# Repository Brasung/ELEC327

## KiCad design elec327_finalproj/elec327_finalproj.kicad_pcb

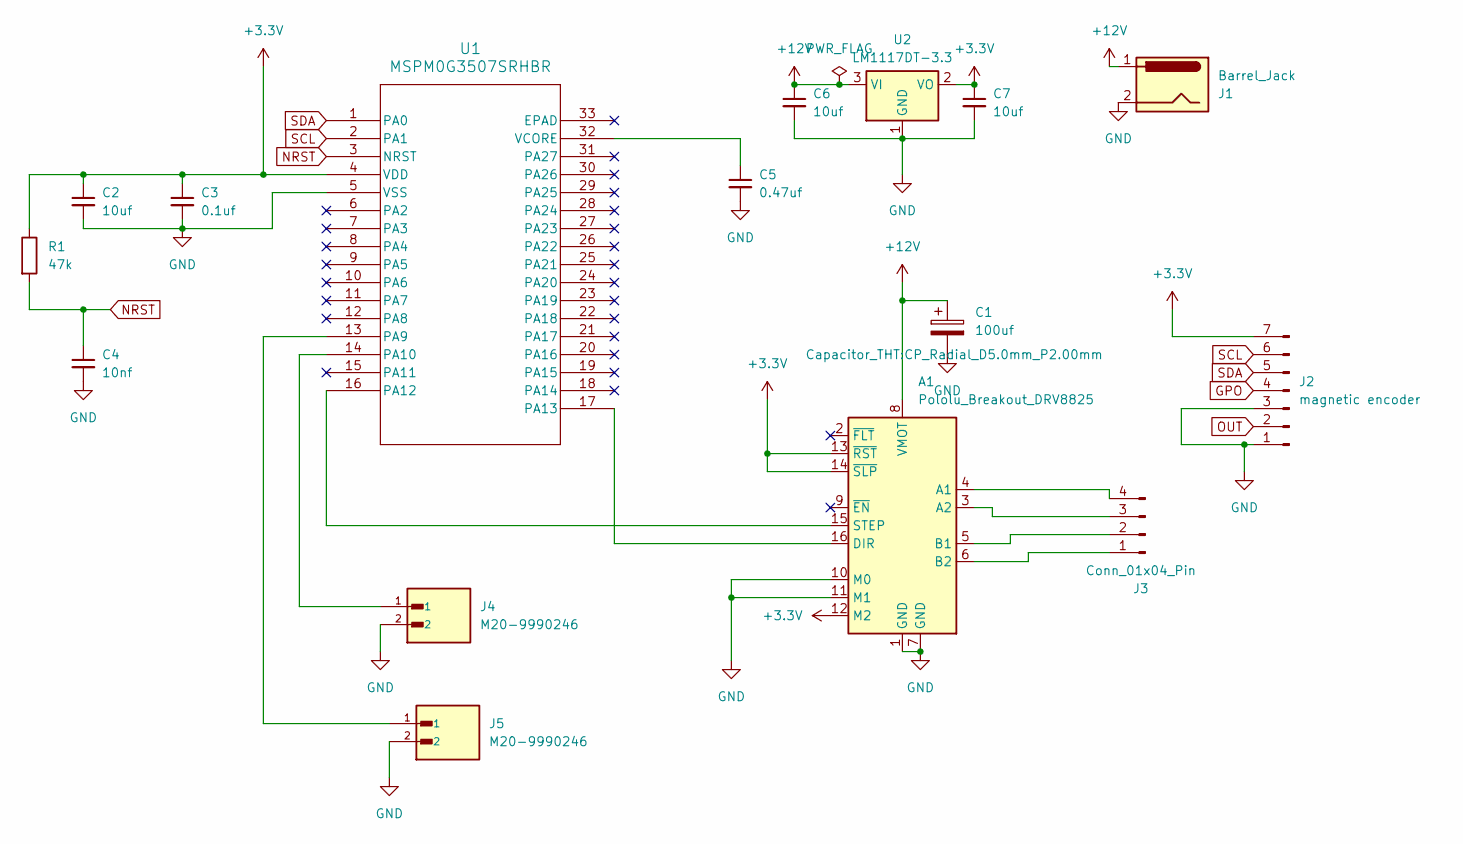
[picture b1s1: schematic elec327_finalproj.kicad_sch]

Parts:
A1: Pololu_Breakout_DRV8825; Pololu_Breakout-16_15.2x20.3mm
C1: 100uf; CP_Radial_D5.0mm_P2.00mm
C2, C6, C7: 10uf; C_0805_2012Metric_Pad1.18x1.45mm_HandSolder
C3: 0.1uf; C_0805_2012Metric_Pad1.18x1.45mm_HandSolder
C4: 10nf; C_0805_2012Metric_Pad1.18x1.45mm_HandSolder
C5: 0.47uf; C_0805_2012Metric_Pad1.18x1.45mm_HandSolder
J1: Barrel_Jack; BarrelJack_SwitchcraftConxall_RAPC10U_Horizontal
J2: magnetic encoder; PinHeader_1x07_P2.54mm_Vertical
J3: Conn_01x04_Pin; PinHeader_1x04_P2.54mm_Vertical
J4, J5: M20-9990246; HARWIN_M20-9990246; PARTREV 14
R1: 47k; R_0805_2012Metric_Pad1.20x1.40mm_HandSolder
U1: MSPM0G3507SRHBR; breakout footprint
U2: LM1117DT-3.3; TO-252-3_TabPin2

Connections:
+3.3V: A1.12 (M2), A1.13 (~RST), A1.14 (~SLP), C2.1, C3.1, C7.1, J2.7, R1.1, U1.4 (VDD), U2.2 (VO)
+12V: A1.8 (VMOT), C1.1, C6.1, J1.1, U2.3 (VI)
GND: A1.1 (GND), A1.7 (GND), A1.10 (M0), A1.11 (M1), C1.2, C2.2, C3.2, C4.2, C5.2, C6.2, C7.2, J1.2, J2.1, J2.3, J4.2, J5.2, U1.5 (VSS), U2.1 (GND)
GPO: J2.4
NRST: C4.1, R1.2, U1.3 (NRST)
unnamed: A1.4 (A1), J3.4
unnamed: A1.3 (A2), J3.3
unnamed: A1.5 (B1), J3.2
unnamed: A1.6 (B2), J3.1
unnamed: A1.16 (DIR), U1.17 (PA13)
unnamed: A1.15 (STEP), U1.16 (PA12)
unnamed: J5.1, U1.13 (PA9)
unnamed: J4.1, U1.14 (PA10)
unnamed: C5.1, U1.32 (VCORE)
OUT: J2.2
SCL: J2.6, U1.2 (PA1)
SDA: J2.5, U1.1 (PA0)

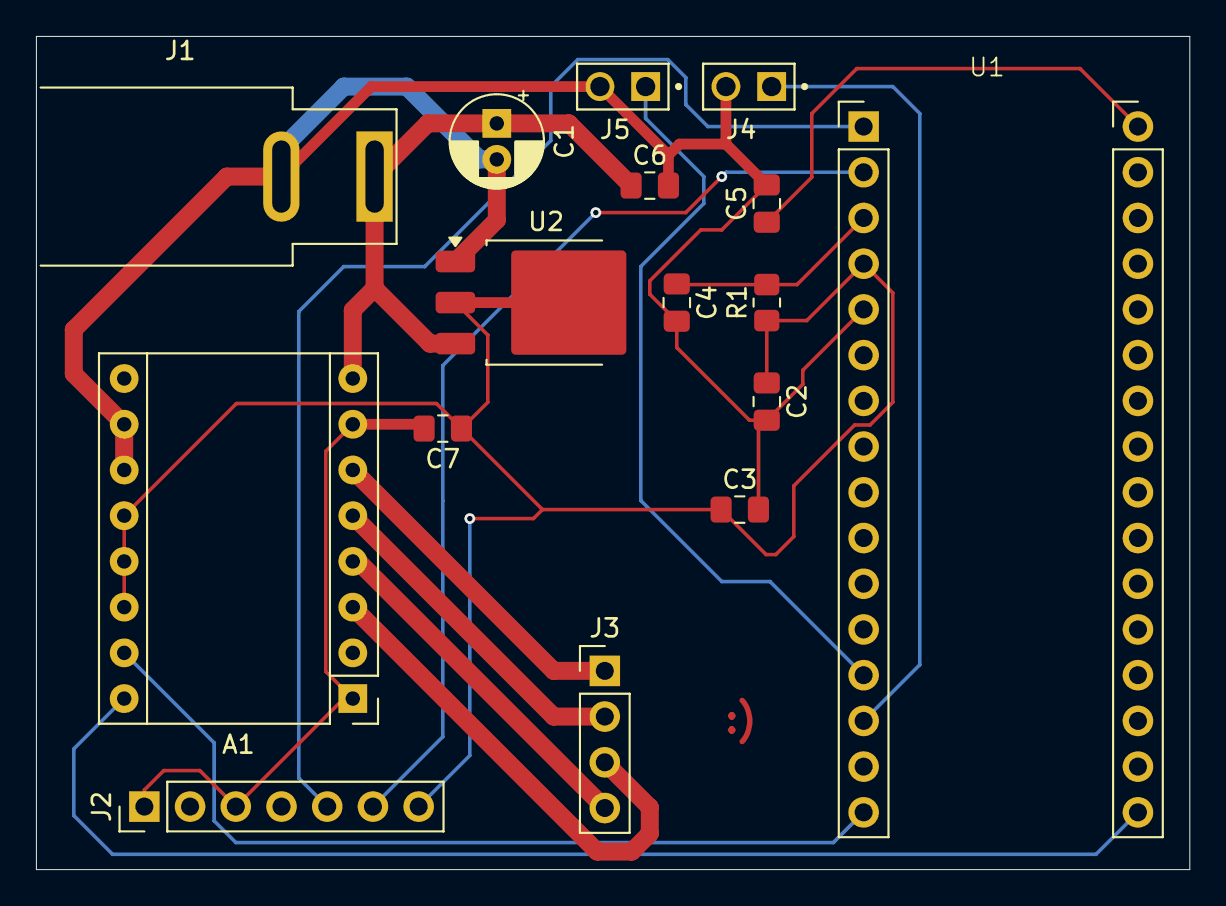
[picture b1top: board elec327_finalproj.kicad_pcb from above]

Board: 2 copper layers, 64.1 x 46.3 mm, 16 parts (0 on the bottom side), 15 nets.

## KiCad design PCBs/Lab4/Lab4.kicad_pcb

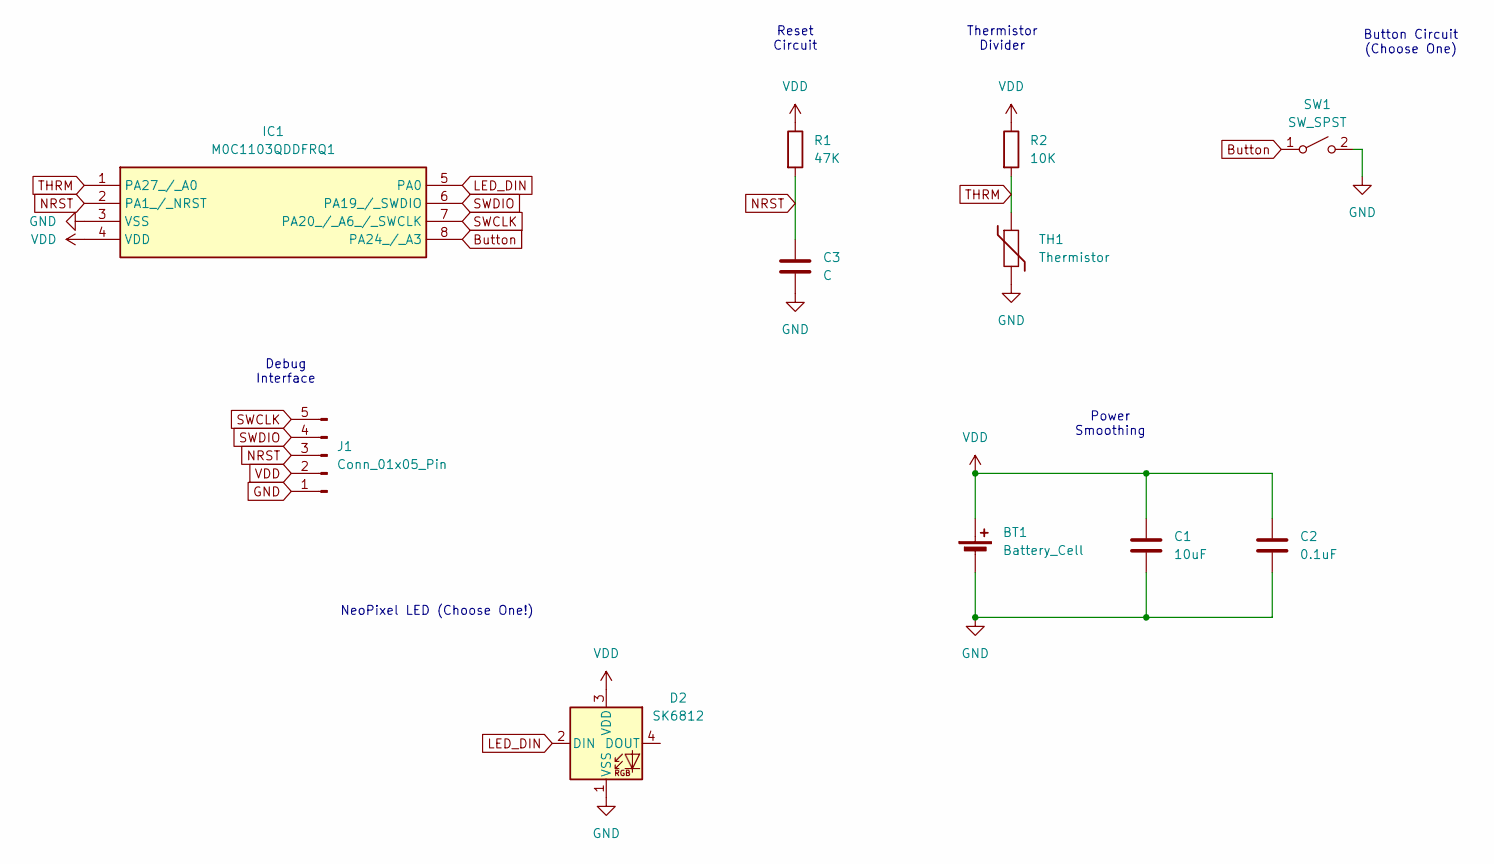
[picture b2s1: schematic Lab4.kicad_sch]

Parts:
BT1: Battery_Cell; BatteryHolder_Keystone_3001_1x12mm
C1: 10uF; C_1206_3216Metric_Pad1.33x1.80mm_HandSolder
C2: 0.1uF; C_1206_3216Metric_Pad1.33x1.80mm_HandSolder
C3: C; C_1206_3216Metric_Pad1.33x1.80mm_HandSolder
D2: SK6812; LED_SK6812_PLCC4_5.0x5.0mm_P3.2mm
IC1: M0C1103QDDFRQ1; SOT-23-8; Mouser Part Number 595-M0C1103QDDFRQ1
J1: Conn_01x05_Pin; PinHeader_1x05_P2.54mm_Vertical
R1: 47K; R_1206_3216Metric_Pad1.30x1.75mm_HandSolder
R2: 10K; R_1206_3216Metric_Pad1.30x1.75mm_HandSolder
SW1: SW_SPST; SW_PUSH_6mm_H5mm
TH1: Thermistor; R_1206_3216Metric_Pad1.30x1.75mm_HandSolder

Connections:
Button: IC1.8 (PA24_/_A3), SW1.1 (A)
GND: BT1.2 (-), C1.2, C2.2, C3.2, D2.1 (VSS), IC1.3 (VSS), J1.1, SW1.2 (B), TH1.2
LED_DIN: D2.2 (DIN), IC1.5 (PA0)
NRST: C3.1, IC1.2 (PA1_/_NRST), J1.3, R1.2
SWCLK: IC1.7 (PA20_/_A6_/_SWCLK), J1.5
SWDIO: IC1.6 (PA19_/_SWDIO), J1.4
THRM: IC1.1 (PA27_/_A0), R2.2, TH1.1
VDD: BT1.1 (+), C1.1, C2.1, D2.3 (VDD), IC1.4 (VDD), J1.2, R1.1, R2.1

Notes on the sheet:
Reset Circuit
NeoPixel LED (Choose One!)
Power Smoothing
Debug Interface
Thermistor Divider
Button Circuit (Choose One)

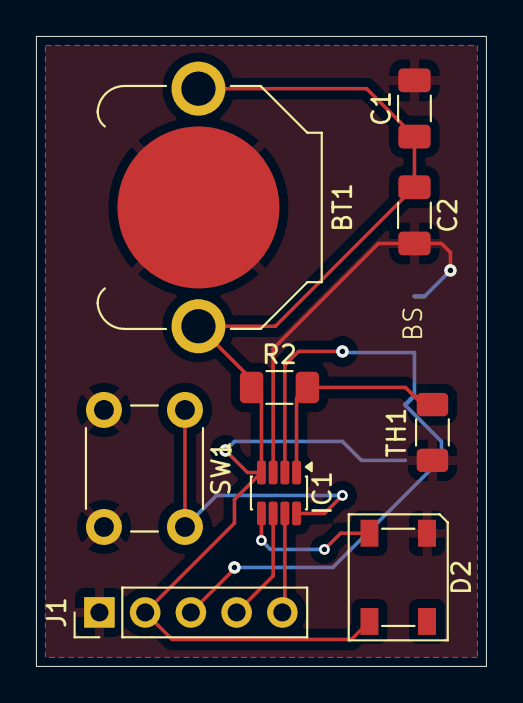
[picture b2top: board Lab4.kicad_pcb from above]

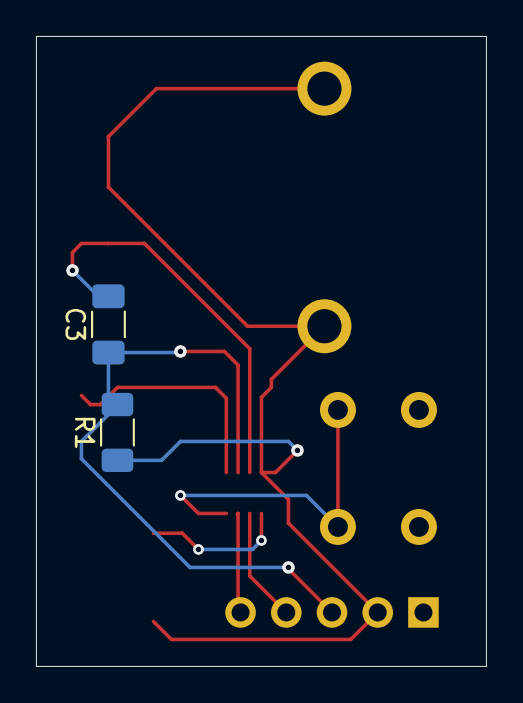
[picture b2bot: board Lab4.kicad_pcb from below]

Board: 2 copper layers, 25.0 x 35.0 mm, 11 parts (2 on the bottom side), 8 nets.

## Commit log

2026-02-09 labs 1-3 working
2026-02-11 resolved lab3 merge conflicts
2026-02-17 Added template code for Lab 5 to workspace
2026-02-18 Routed initial pcb submission
2026-02-19 Updated lab 5 template to fix missing delay.c
2026-02-20 2026 updated name for Simon PCB
2026-02-21 Fixed routing for final submission
2026-02-22 Fixed a typo - DisableimerA1PWM->DisableTimerA1PWM
2026-03-02 lab5 submission
2026-03-08 copied lab 5 functionality to lab 6
2026-03-23 lab 6 final
2026-03-30 Lab 8 rough draft
2026-03-30 Fixed missing lab 8 main
2026-04-01 Updated Lab 8 code
2026-04-01 Updated comments and color
2026-04-01 Updated TRM and moved Lab8 to Lab7
2026-04-01 add button response and startup song
2026-04-07 simon final
2026-04-18 Added power test firmware
2026-04-20 final project pcb
